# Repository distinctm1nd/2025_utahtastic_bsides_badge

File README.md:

# 2025 Utahtastic BSides Badge

Key Features:

    - ESP32-S3-WROOM Microcontroller
    - LoRa 
    - 25 Addressable LEDs
    - TFT Display
    - Power Options: Powered via Micro USB or 3 AA batteries (regulated at 3.3V).
    - Hackable and Programmable: Easily program with just a laptop and a Micro USB cable.
    - Expansion Ready: 3 minibadge slots for future add-ons.
    - Custom Meshtastic Firmware: Open-source firmware designed for mesh networking.
    - Convenient Controls – UART connection point, Reset and Flash buttons, and a power switch for toggling between USB and battery modes.
    - 4 GPIO pins available for custom dev work​

## Make sure you have the following items:

- Badge
- 6 Minibadge headers
- Battery holder
- Moon LED diffuser
- 3 AA Batteries
- Lanyard
- Minibadge kit
- Double sided foam tape

## Badge Assembly

The badge does not require further assembly to be functional by powering through the USB with an external battery. Make sure that the switch is at USB if powering with USB. 

To complete the assembly, first solder the minibadge headers to the badge. Be careful while soldering the header that is near the display. 

After this, solder the battery holder and apply foam tape to hold the end without solder connectors in place. 

Use hot glue to attach the moon diffuser to moon on the back of the badge. 

Attach the lanyard to the "post" by the raven. 

## Minibadge Assembly

- Solder the 68 ohm (1206) resistors to R1 and R2. These can be oriented any direction. 
- Solder the LEDs (yellow) to D1, D2, D3 and D4. Orientation on these matters. The green mark is on the cathode side of the LED so it needs to be oriented toward the cathode side on the PCB. The cathode side on the PCB is marked by a box around it. 

- Solder the headers to the four corners. 

## Keyboard Functionality

5-Way Switch
- Up: send message
- Down: erase/backspace
- Left: move cursor left
- Right: move cursor right
- Press: switch screens

## STL Files for joystick button cap and moon diffuser

[Joystick Button Cap](https://www.printables.com/model/1166931-joystick-cap-for-b-sides-utah-2025-badge)

[Moon Diffuser](https://www.printables.com/model/1166783-moon-led-diffuser-for-b-sides-utah-2025-badge)

## A few notes on usage

Don't transmit without the antenna attached as you could damage the badge. 

If you download the meshtastic app you can connect to your badge via bluetooth and send /receive messages through the app. You can also change many setting through the app. 

Make sure that you are on the Medium Fast channel for the conference. 

To change the moon LED color or brightness, in the app, go to:
- Radio Configuration -> Ambient Lighting

Once in the ambient lighting config you can change the brightness of the moon LEDs by changing "Current" to a different number. 255 is max brightness and anything less than that is dimmer. You can change the color codes for Red, Green and Blue to generate different colors. 

If you can't send or receive messages make sure that the LoRa channel is not on long fast. For the conference we'll be using medium fast. 

If the badge doesn't start up when turned on then push the reset button.

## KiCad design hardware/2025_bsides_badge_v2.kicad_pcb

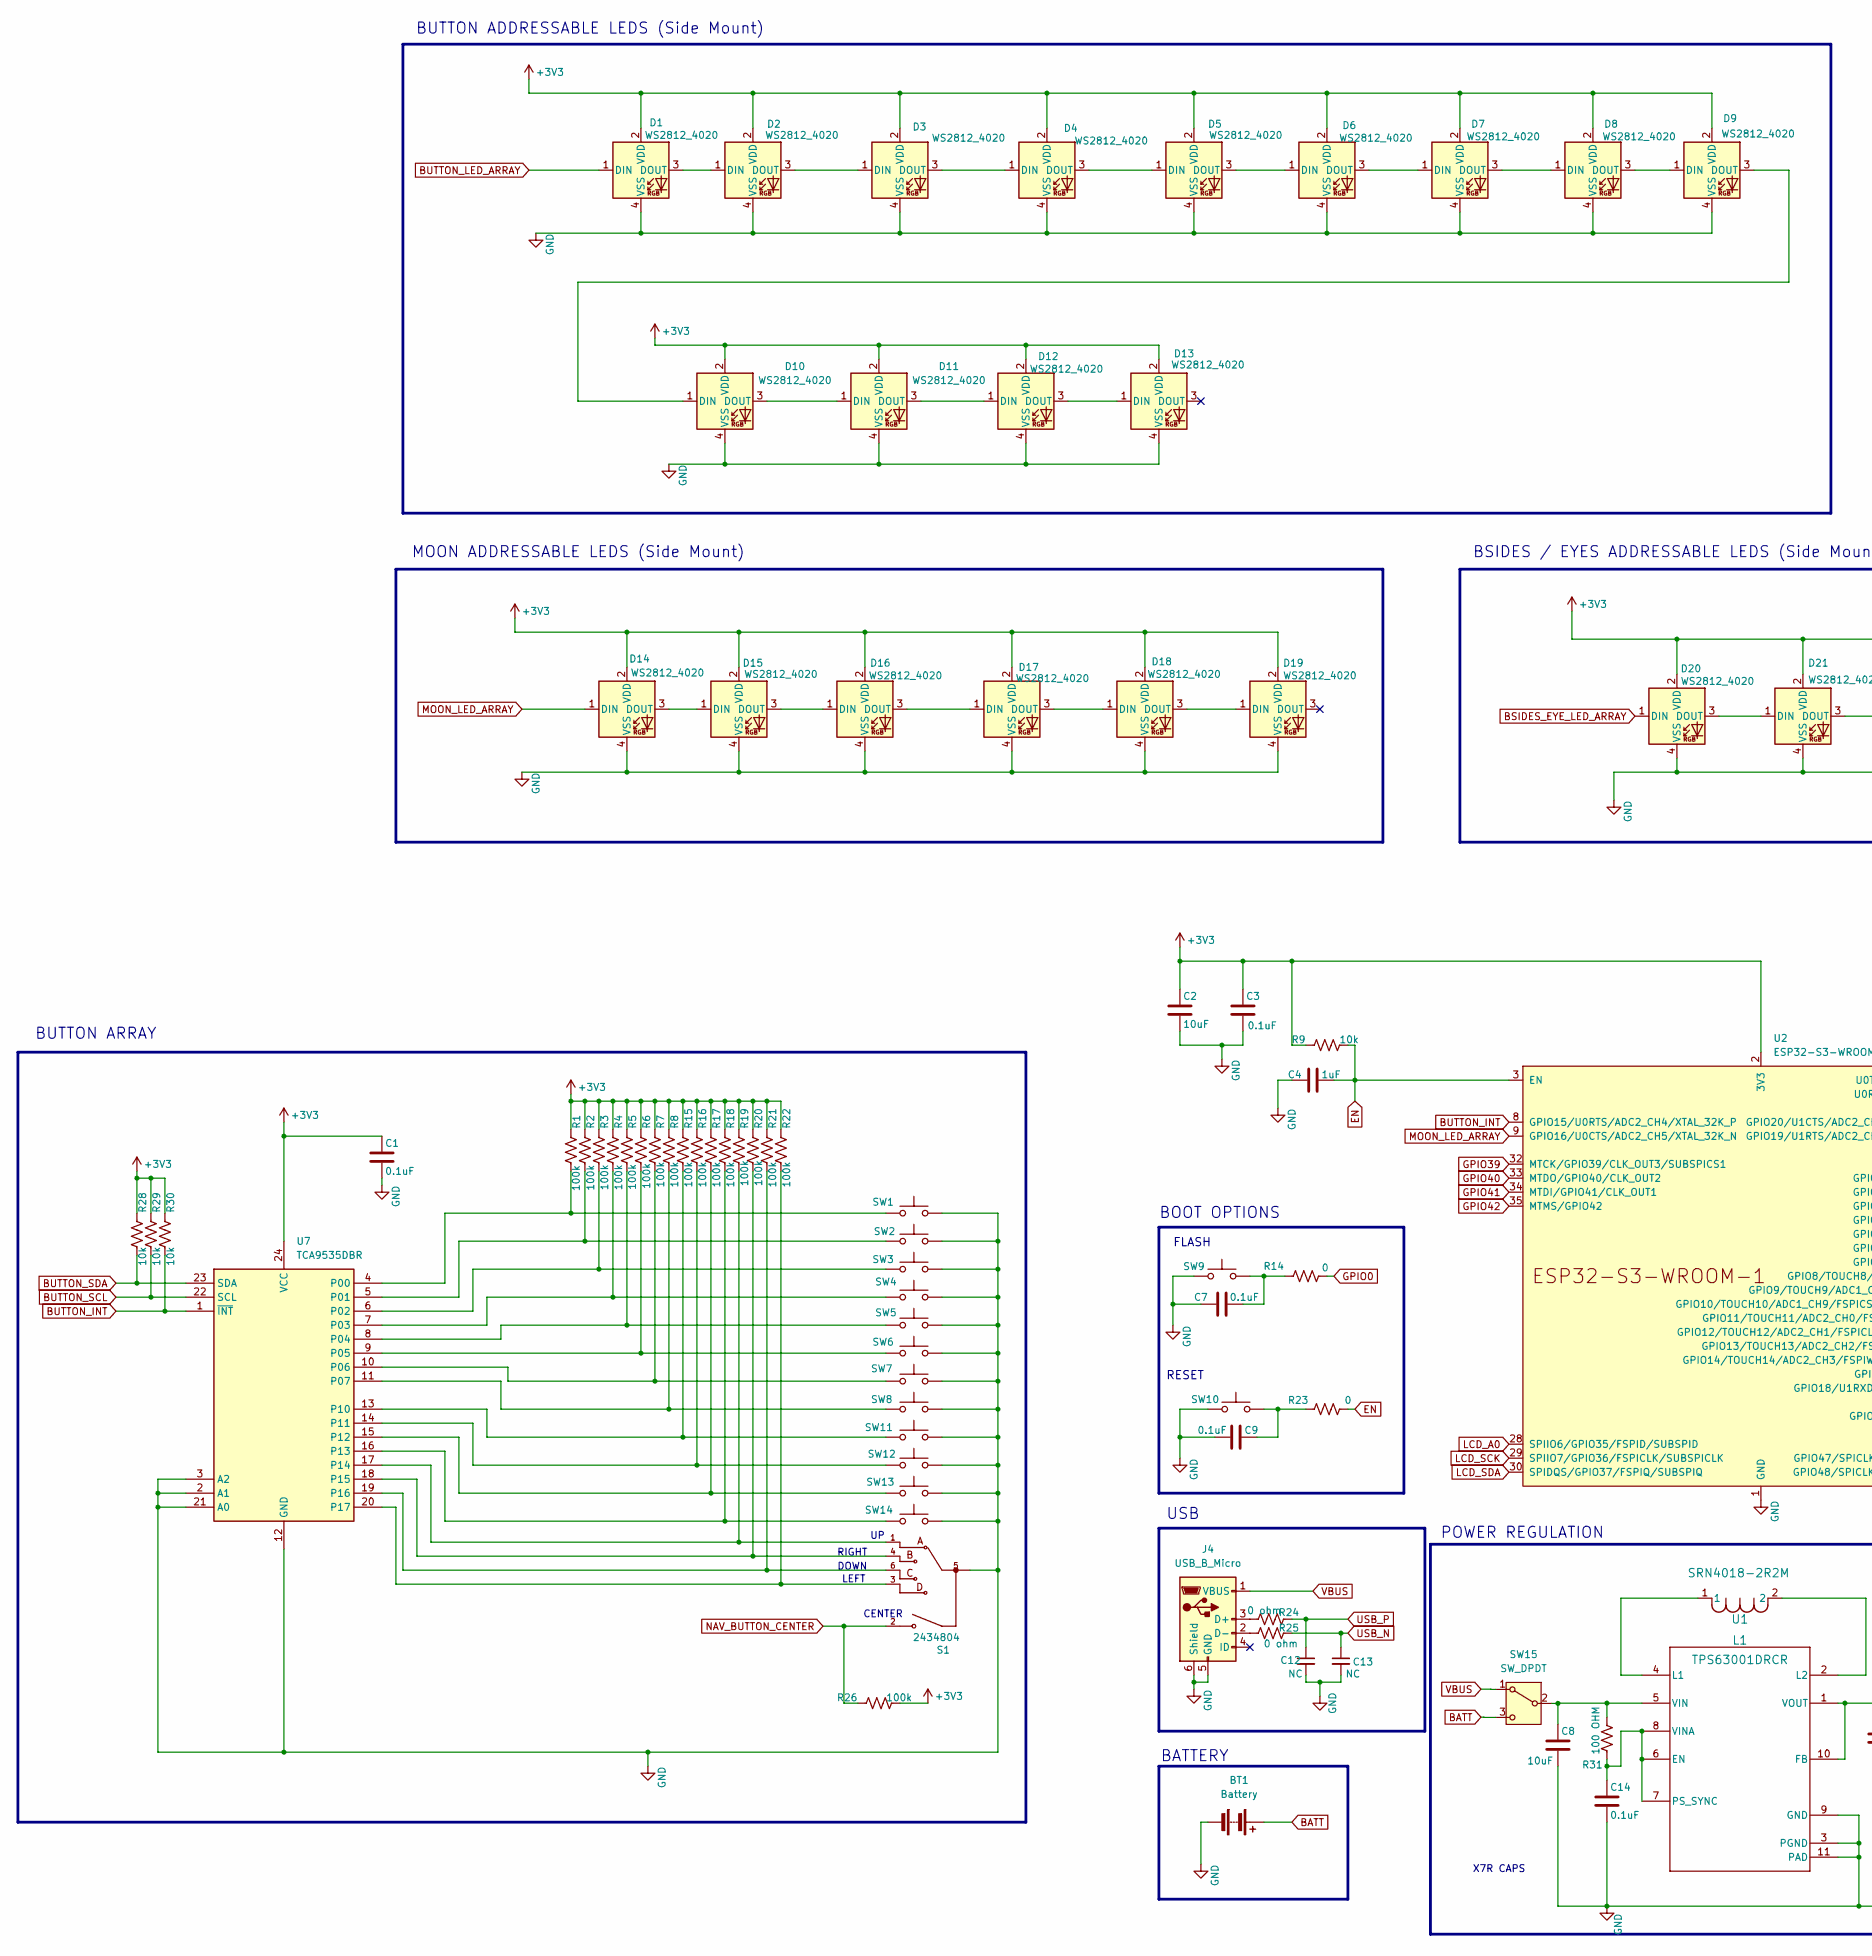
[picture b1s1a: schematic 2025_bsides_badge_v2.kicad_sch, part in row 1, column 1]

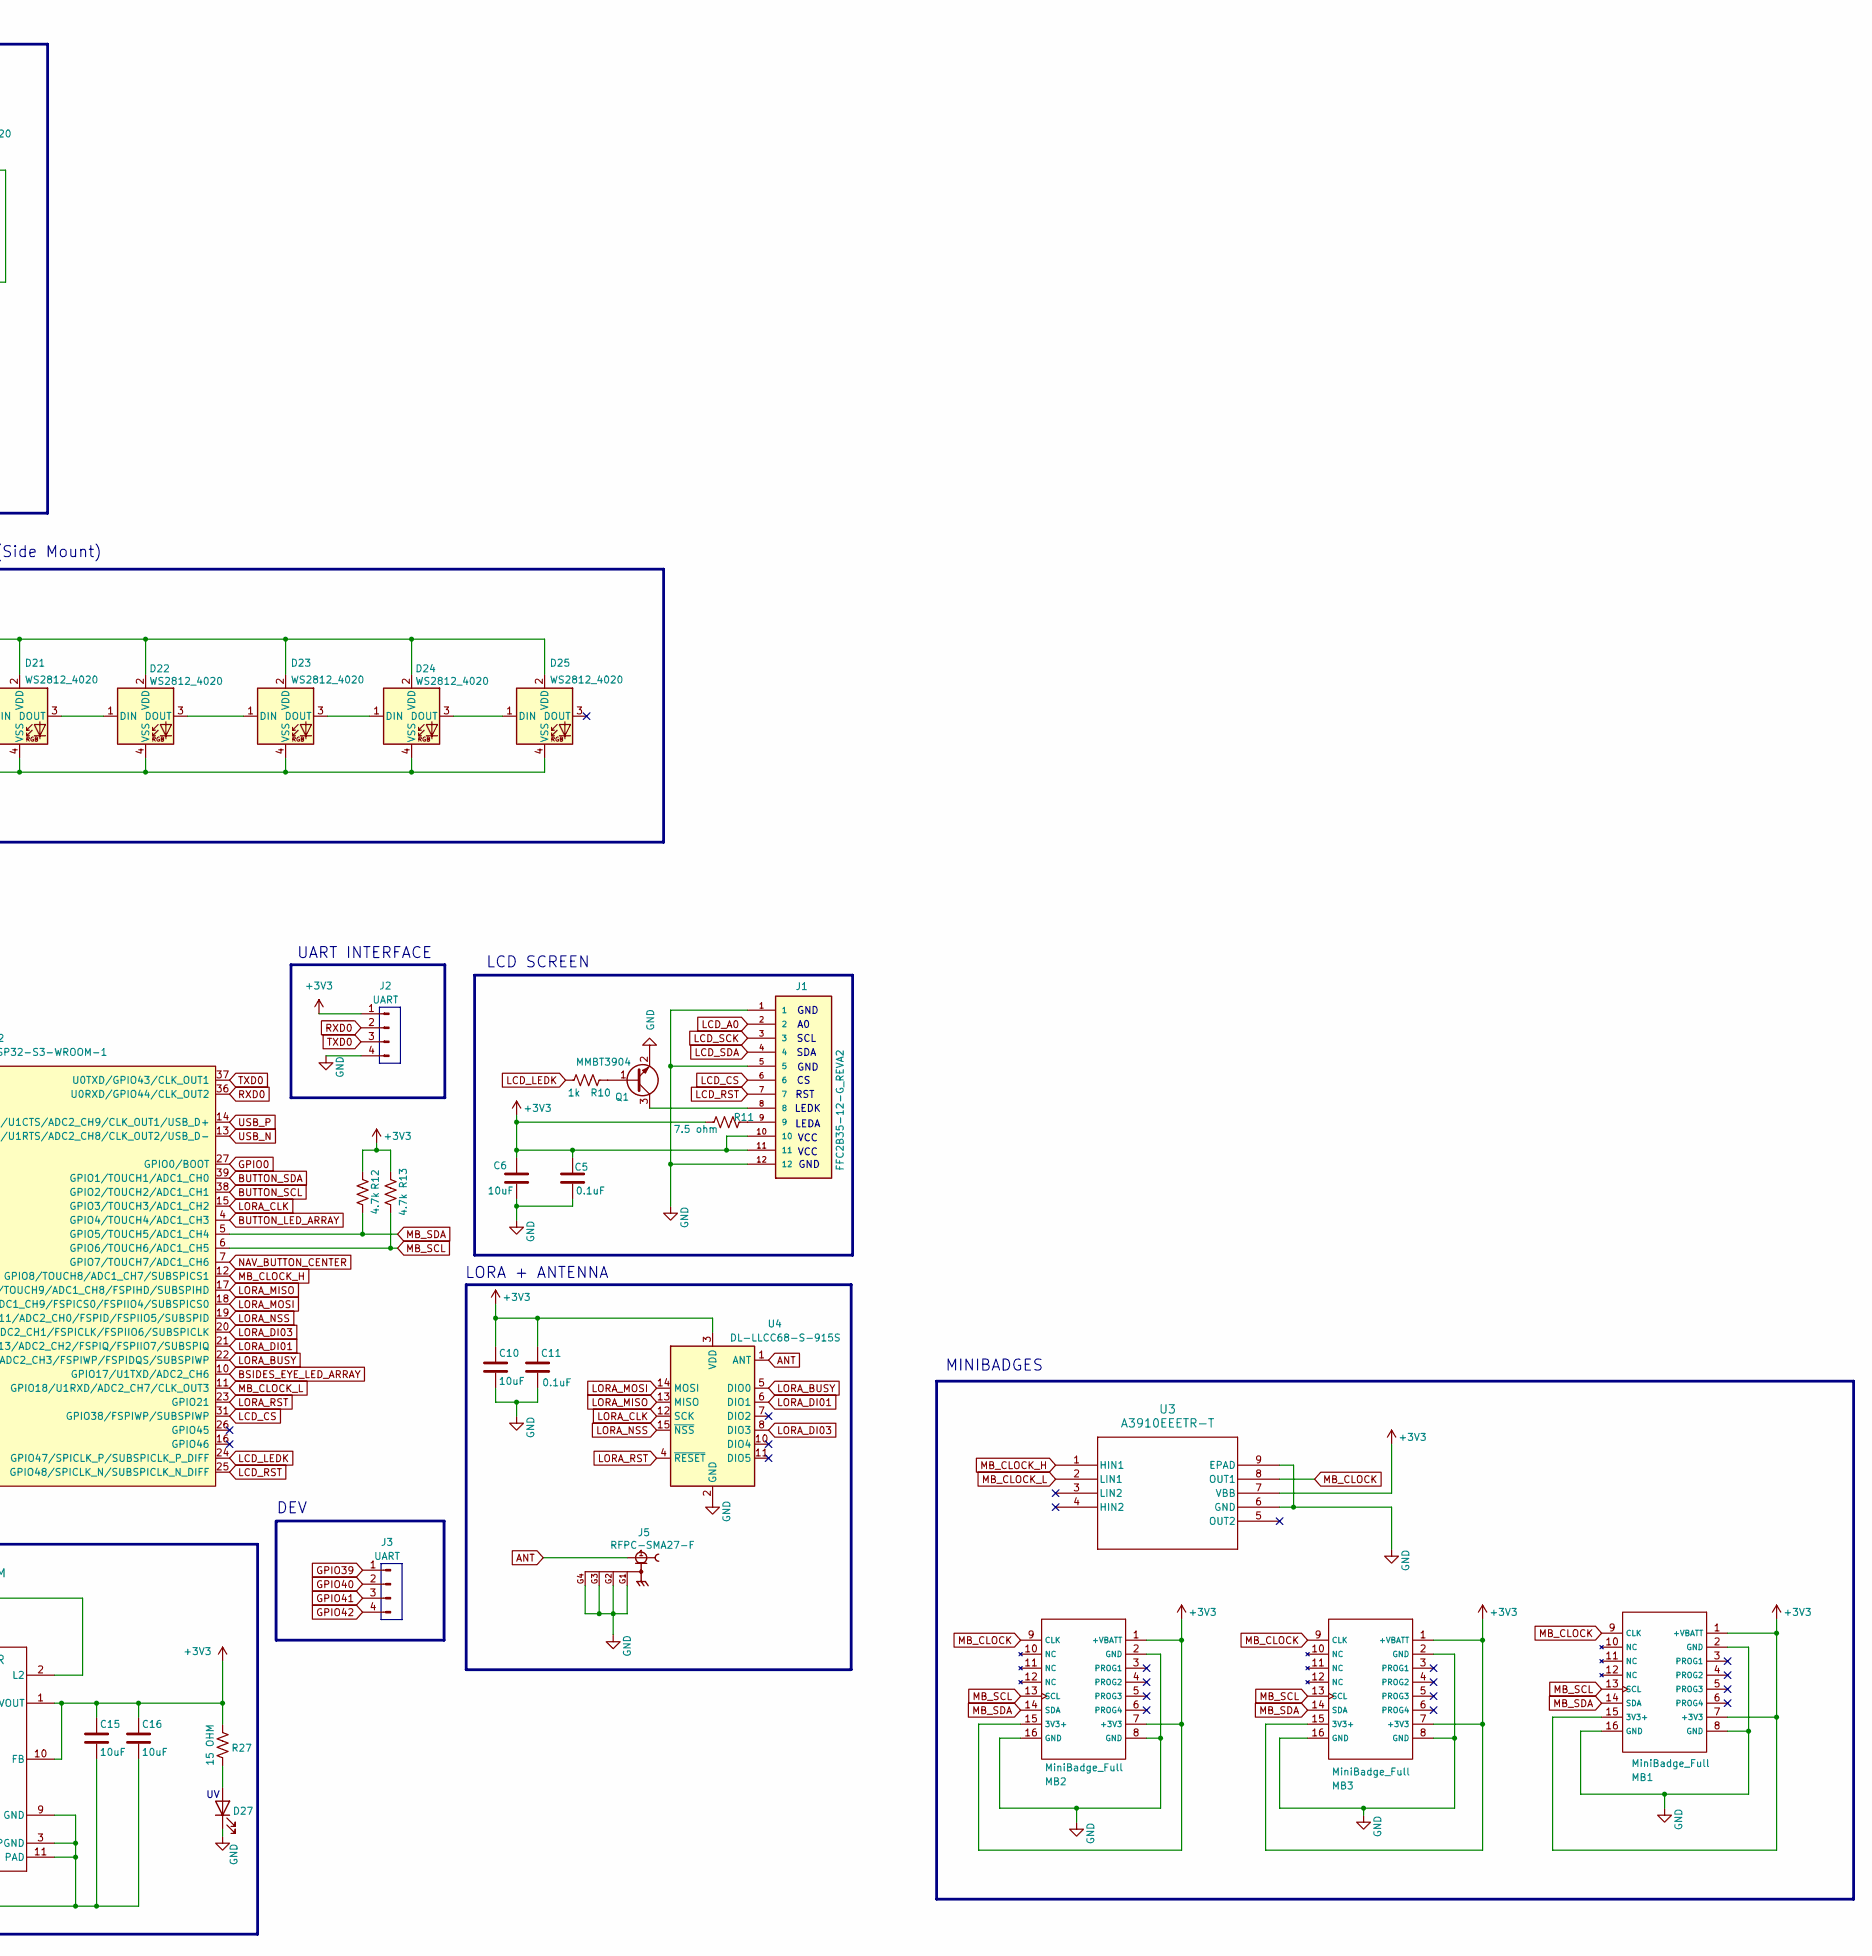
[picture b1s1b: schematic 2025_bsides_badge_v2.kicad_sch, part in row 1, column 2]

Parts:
BT1: Battery; mad_hatter_3_AA_battery
C1, C3, C5, C7, C9, C11, C14: 0.1uF; C_0603_1608Metric_Pad1.08x0.95mm_HandSolder
C2, C6, C8, C10, C15, C16: 10uF; C_0805_2012Metric_Pad1.18x1.45mm_HandSolder
C4: 1uF; C_0603_1608Metric_Pad1.08x0.95mm_HandSolder
C12, C13: NC; C_0603_1608Metric_Pad1.08x0.95mm_HandSolder
D1, D2, D3, D4, D5, D6, D7, D8, D9, D10, D11, D12, D13, D14, D15, D16, D17, D18, D19, D20, D21, D22, D23, D24, D25: WS2812_4020; sk6812-side-a
D27: LED; LED_1206_3216Metric_Pad1.42x1.75mm_HandSolder
J1: FFC2B35-12-G_REVA2; GCT_FFC2B35-12-G_REVA2; PARTREV A2
J2, J3: UART; mad_hatter_sneaky_uart_connector
J4: USB_B_Micro; USB_Micro-B_Amphenol_10118193-0001LF_Horizontal
J5: RFPC-SMA27-F; bsides_RFPC_SMA27_F; PARTREV 1.0
L1: SRN4018-2R2M; L_Bourns-SRN4018
MB1, MB2, MB3: MiniBadge_Full; MiniBadge_Slot_Basic
Q1: MMBT3904; SOT-23
R1, R2, R3, R4, R5, R6, R7, R8, R15, R16, R17, R18, R19, R20, R21, R22, R26: 100k; R_0603_1608Metric_Pad0.98x0.95mm_HandSolder
R9, R28, R29, R30: 10k; R_0603_1608Metric_Pad0.98x0.95mm_HandSolder
R10: 1k; R_0603_1608Metric_Pad0.98x0.95mm_HandSolder
R11: 7.5 ohm; R_0603_1608Metric_Pad0.98x0.95mm_HandSolder
R12, R13: 4.7k; R_0603_1608Metric_Pad0.98x0.95mm_HandSolder
R14, R23: 0; R_0603_1608Metric_Pad0.98x0.95mm_HandSolder
R24, R25: 0 ohm; R_0603_1608Metric_Pad0.98x0.95mm_HandSolder
R27: 15 OHM; R_0603_1608Metric_Pad0.98x0.95mm_HandSolder
R31: 100 OHM; R_0603_1608Metric_Pad0.98x0.95mm_HandSolder
S1: 2434804; nav_switch_2434804_1; PARTREV A
SW1, SW2, SW3, SW4, SW5, SW6, SW7, SW8, SW9, SW10, SW11, SW12, SW13, SW14: SW_Push; button_switch_TL3305A
SW15: SW_DPDT; js202011jaqn
U1: TPS63001DRCR; Texas_DRC0010J
U2: ESP32-S3-WROOM-1
U3: A3910EEETR-T; DFN-8_ALM
U4: DL-LLCC68-S-915S; Ai-Thinker-Ra-01-LoRa
U7: TCA9535DBR; SSOP-24_5.3x8.2mm_P0.65mm

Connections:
+3V3: C1.1, C2.1, C3.1, C5.1, C6.1, C10.1, C11.1, C15.1, C16.1, D1.2 (VDD), D2.2 (VDD), D3.2 (VDD), D4.2 (VDD), D5.2 (VDD), D6.2 (VDD), D7.2 (VDD), D8.2 (VDD), D9.2 (VDD), D10.2 (VDD), D11.2 (VDD), D12.2 (VDD), D13.2 (VDD), D14.2 (VDD), D15.2 (VDD), D16.2 (VDD), D17.2 (VDD), D18.2 (VDD), D19.2 (VDD), D20.2 (VDD), D21.2 (VDD), D22.2 (VDD), D23.2 (VDD), D24.2 (VDD), D25.2 (VDD), J1.10, J1.11, J2.1, MB1.1 (+VBATT), MB1.7 (+3V3), MB1.15 (3V3+), MB2.1 (+VBATT), MB2.7 (+3V3), MB2.15 (3V3+), MB3.1 (+VBATT), MB3.7 (+3V3), MB3.15 (3V3+), R1.1, R2.1, R3.1, R4.1, R5.1, R6.1, R7.1, R8.1, R9.1, R11.1, R12.2, R13.2, R15.1, R16.1, R17.1, R18.1, R19.1, R20.1, R21.1, R22.1, R26.2, R27.1, R28.1, R29.1, R30.1, U1.1 (VOUT), U1.10 (FB), U2.2 (3V3), U3.7 (VBB), U4.3 (VDD), U7.24 (VCC)
ANT: J5.1, U4.1 (ANT)
BATT: BT1.1 (+), SW15.3 (C)
BSIDES_EYE_LED_ARRAY: D20.1 (DIN), U2.10 (GPIO17/U1TXD/ADC2_CH6)
BUTTON_INT: R30.2, U2.8 (GPIO15/U0RTS/ADC2_CH4/XTAL_32K_P), U7.1 (~INT)
BUTTON_LED_ARRAY: D1.1 (DIN), U2.4 (GPIO4/TOUCH4/ADC1_CH3)
BUTTON_SCL: R29.2, U2.38 (GPIO2/TOUCH2/ADC1_CH1), U7.22 (SCL)
BUTTON_SDA: R28.2, U2.39 (GPIO1/TOUCH1/ADC1_CH0), U7.23 (SDA)
EN: C4.1, R9.2, R23.2, U2.3 (EN)
GND: BT1.2 (-), C1.2, C2.2, C3.2, C4.2, C5.2, C6.2, C7.2, C8.2, C9.2, C10.2, C11.2, C12.2, C13.2, C14.2, C15.2, C16.2, D1.4 (VSS), D2.4 (VSS), D3.4 (VSS), D4.4 (VSS), D5.4 (VSS), D6.4 (VSS), D7.4 (VSS), D8.4 (VSS), D9.4 (VSS), D10.4 (VSS), D11.4 (VSS), D12.4 (VSS), D13.4 (VSS), D14.4 (VSS), D15.4 (VSS), D16.4 (VSS), D17.4 (VSS), D18.4 (VSS), D19.4 (VSS), D20.4 (VSS), D21.4 (VSS), D22.4 (VSS), D23.4 (VSS), D24.4 (VSS), D25.4 (VSS), D27.1 (K), J1.1, J1.5, J1.12, J2.4, J4.5 (GND), J4.6 (Shield), J5.G1, J5.G2, J5.G3, J5.G4, MB1.2 (GND), MB1.8 (GND), MB1.16 (GND), MB2.2 (GND), MB2.8 (GND), MB2.16 (GND), MB3.2 (GND), MB3.8 (GND), MB3.16 (GND), Q1.2 (E), S1.5, SW1.2, SW2.2, SW3.2, SW4.2, SW5.2, SW6.2, SW7.2, SW8.2, SW9.1, SW10.1, SW11.2, SW12.2, SW13.2, SW14.2, U1.3 (PGND), U1.9 (GND), U1.11 (PAD), U2.1 (GND), U2.40 (GND), U2.41 (GND), U3.6 (GND), U3.9 (EPAD), U4.2 (GND), U4.9 (GND), U4.16 (GND), U7.2 (A1), U7.3 (A2), U7.12 (GND), U7.21 (A0)
GPIO0: R14.2, U2.27 (GPIO0/BOOT)
GPIO39: J3.1, U2.32 (MTCK/GPIO39/CLK_OUT3/SUBSPICS1)
GPIO40: J3.2, U2.33 (MTDO/GPIO40/CLK_OUT2)
GPIO41: J3.3, U2.34 (MTDI/GPIO41/CLK_OUT1)
GPIO42: J3.4, U2.35 (MTMS/GPIO42)
LCD_A0: J1.2, U2.28 (SPIIO6/GPIO35/FSPID/SUBSPID)
LCD_CS: J1.6, U2.31 (GPIO38/FSPIWP/SUBSPIWP)
LCD_LEDK: R10.1, U2.24 (GPIO47/SPICLK_P/SUBSPICLK_P_DIFF)
LCD_RST: J1.7, U2.25 (GPIO48/SPICLK_N/SUBSPICLK_N_DIFF)
LCD_SCK: J1.3, U2.29 (SPIIO7/GPIO36/FSPICLK/SUBSPICLK)
LCD_SDA: J1.4, U2.30 (SPIDQS/GPIO37/FSPIQ/SUBSPIQ)
LORA_BUSY: U2.22 (GPIO14/TOUCH14/ADC2_CH3/FSPIWP/FSPIDQS/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), U4.5 (DIO0)
LORA_CLK: U2.15 (GPIO3/TOUCH3/ADC1_CH2), U4.12 (SCK)
LORA_DI01: U2.21 (GPIO13/TOUCH13/ADC2_CH2/FSPIQ/FSPIIO7/S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), U4.6 (DIO1)
LORA_DI03: U2.20 (GPIO12/TOUCH12/ADC2_CH1/FSPICLK/FSPIIO6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), U4.8 (DIO3)
LORA_MISO: U2.17 (GPIO9/TOUCH9/ADC1_CH8/FSPIHD/SUBSPIHD), U4.13 (MISO)
LORA_MOSI: U2.18 (GPIO10/TOUCH10/ADC1_CH9/FSPICS0/FSPIIO4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), U4.14 (MOSI)
LORA_NSS: U2.19 (GPIO11/TOUCH11/ADC2_CH0/FSPID/FSPIIO5/S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), U4.15 (~NSS)
LORA_RST: U2.23 (GPIO21), U4.4 (~RESET)
MB_CLOCK: MB1.9 (CLK), MB2.9 (CLK), MB3.9 (CLK), U3.8 (OUT1)
MB_CLOCK_H: U2.12 (GPIO8/TOUCH8/ADC1_CH7/SUBSPICS1), U3.1 (HIN1)
MB_CLOCK_L: U2.11 (GPIO18/U1RXD/ADC2_CH7/CLK_OUT3), U3.2 (LIN1)
MB_SCL: MB1.13 (SCL), MB2.13 (SCL), MB3.13 (SCL), R13.1, U2.6 (GPIO6/TOUCH6/ADC1_CH5)
MB_SDA: MB1.14 (SDA), MB2.14 (SDA), MB3.14 (SDA), R12.1, U2.5 (GPIO5/TOUCH5/ADC1_CH4)
MOON_LED_ARRAY: D14.1 (DIN), U2.9 (GPIO16/U0CTS/ADC2_CH5/XTAL_32K_N)
NAV_BUTTON_CENTER: R26.1, S1.2, U2.7 (GPIO7/TOUCH7/ADC1_CH6)
unnamed: C7.1, R14.1, SW9.2
unnamed: C9.1, R23.1, SW10.2
unnamed: D1.3 (DOUT), D2.1 (DIN)
unnamed: D2.3 (DOUT), D3.1 (DIN)
unnamed: D3.3 (DOUT), D4.1 (DIN)
unnamed: D4.3 (DOUT), D5.1 (DIN)
unnamed: D5.3 (DOUT), D6.1 (DIN)
unnamed: D6.3 (DOUT), D7.1 (DIN)
unnamed: D7.3 (DOUT), D8.1 (DIN)
unnamed: D8.3 (DOUT), D9.1 (DIN)
unnamed: D9.3 (DOUT), D10.1 (DIN)
unnamed: D10.3 (DOUT), D11.1 (DIN)
unnamed: D11.3 (DOUT), D12.1 (DIN)
unnamed: D12.3 (DOUT), D13.1 (DIN)
unnamed: D14.3 (DOUT), D15.1 (DIN)
unnamed: D15.3 (DOUT), D16.1 (DIN)
unnamed: D16.3 (DOUT), D17.1 (DIN)
unnamed: D17.3 (DOUT), D18.1 (DIN)
unnamed: D18.3 (DOUT), D19.1 (DIN)
unnamed: D20.3 (DOUT), D21.1 (DIN)
unnamed: D21.3 (DOUT), D22.1 (DIN)
unnamed: D22.3 (DOUT), D23.1 (DIN)
unnamed: D23.3 (DOUT), D24.1 (DIN)
unnamed: D24.3 (DOUT), D25.1 (DIN)
unnamed: D27.2 (A), R27.2
unnamed: J1.9, R11.2
unnamed: J4.3 (D+), R24.2
unnamed: J4.2 (D-), R25.2
unnamed: Q1.1 (B), R10.2
unnamed: J1.8, Q1.3 (C)
unnamed: C8.1, R31.1, SW15.2 (B), U1.5 (VIN)
unnamed: C14.1, R31.2, U1.6 (EN), U1.7 (PS_SYNC), U1.8 (VINA)
unnamed: L1.1, U1.4 (L1)
unnamed: L1.2, U1.2 (L2)
unnamed: R1.2, SW1.1, U7.4 (P00)
unnamed: R2.2, SW2.1, U7.5 (P01)
unnamed: R3.2, SW3.1, U7.6 (P02)
unnamed: R4.2, SW4.1, U7.7 (P03)
unnamed: R5.2, SW5.1, U7.8 (P04)
unnamed: R6.2, SW6.1, U7.9 (P05)
unnamed: R7.2, SW7.1, U7.10 (P06)
unnamed: R8.2, SW8.1, U7.11 (P07)
unnamed: R15.2, SW11.1, U7.13 (P10)
unnamed: R16.2, SW12.1, U7.14 (P11)
unnamed: R17.2, SW13.1, U7.15 (P12)
unnamed: R18.2, SW14.1, U7.16 (P13)
unnamed: R19.2, S1.1, U7.17 (P14)
unnamed: R20.2, S1.4, U7.18 (P15)
unnamed: R21.2, S1.6, U7.19 (P16)
unnamed: R22.2, S1.3, U7.20 (P17)
RXD0: J2.2, U2.36 (U0RXD/GPIO44/CLK_OUT2)
TXD0: J2.3, U2.37 (U0TXD/GPIO43/CLK_OUT1)
USB_N: C13.1, R25.1, U2.13 (GPIO19/U1RTS/ADC2_CH8/CLK_OUT2/USB_D-)
USB_P: C12.1, R24.1, U2.14 (GPIO20/U1CTS/ADC2_CH9/CLK_OUT1/USB_D+)
VBUS: J4.1 (VBUS), SW15.1 (A)

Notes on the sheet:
UART INTERFACE
LORA + ANTENNA
BATTERY
LEFT
MINIBADGES
GND
DEV
USB
BUTTON ARRAY
VCC
FLASH
LCD SCREEN
MOON ADDRESSABLE LEDS (Side Mount)
POWER REGULATION
BSIDES / EYES ADDRESSABLE LEDS (Side Mount)
RESET
X7R CAPS
CENTER
BUTTON ADDRESSABLE LEDS (Side Mount)
DOWN
SDA
LEDA
BOOT OPTIONS
RIGHT
RST
SCL
LEDK

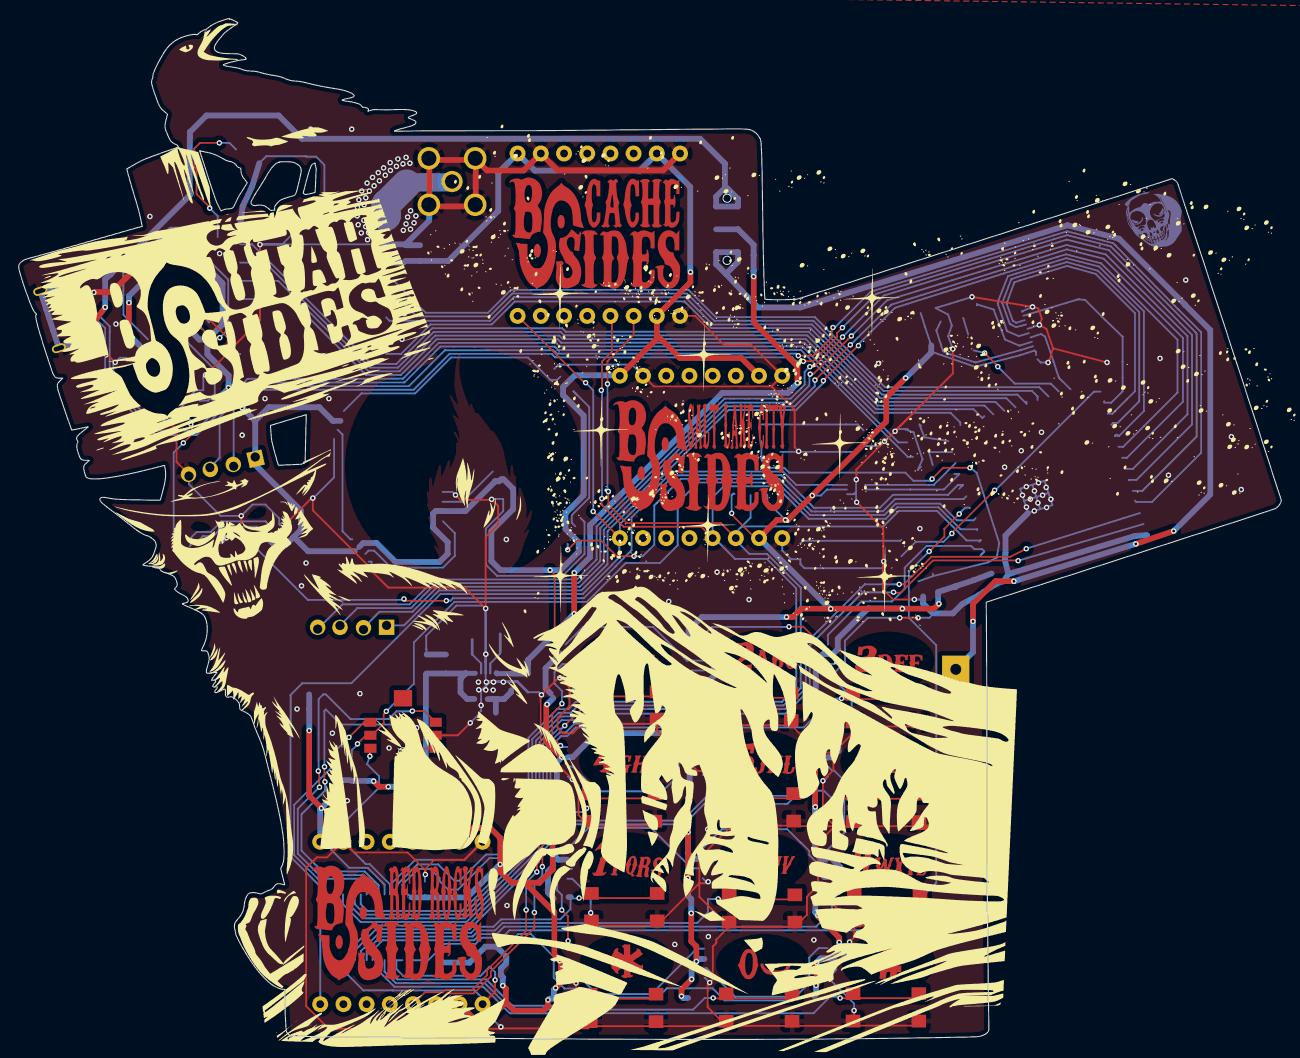
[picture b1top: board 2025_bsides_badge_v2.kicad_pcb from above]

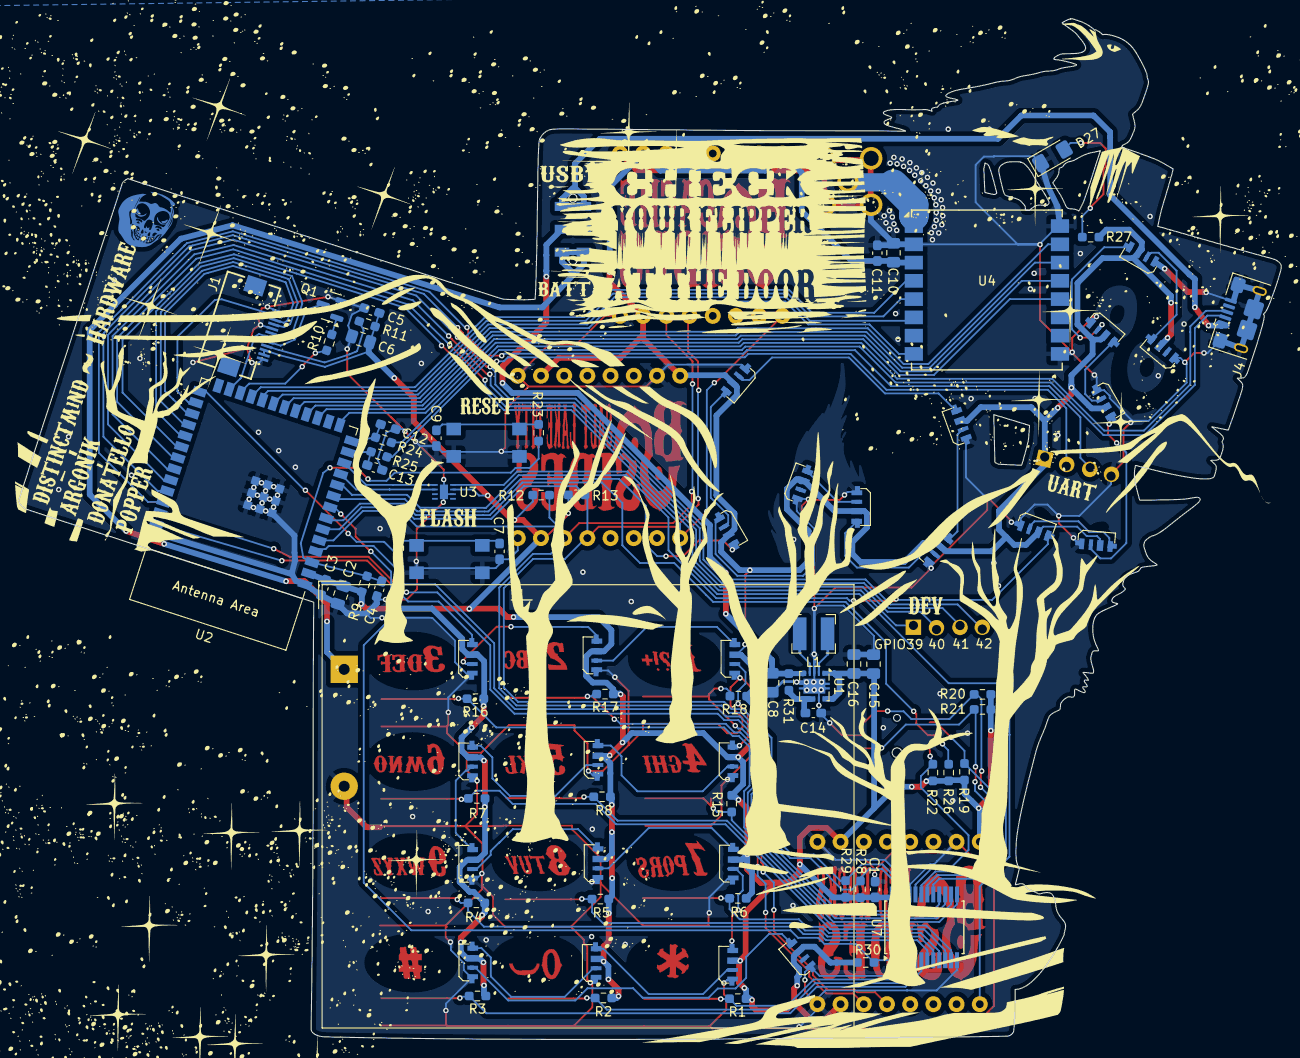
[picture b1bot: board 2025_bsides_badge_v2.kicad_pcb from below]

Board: 2 copper layers, 138.2 x 111.8 mm, 105 parts (85 on the bottom side), 91 nets.

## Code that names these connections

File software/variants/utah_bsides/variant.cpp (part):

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
// I2C Expander (TCA9535)
#define TCA9535_ADDRESS 0x20
#define BUTTON_SDA 1
#define BUTTON_SCL 2
#define BUTTON_INT 15

extern graphics::Screen *screen;

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    TickType_t xLastWakeTime;
    xLastWakeTime = xTaskGetTickCount();

    pinMode(MB_CLOCK_H, OUTPUT);
    pinMode(MB_CLOCK_L, OUTPUT);

    while (1){ 
        //Update Minibadge CLK pin
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
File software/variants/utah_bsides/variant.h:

//////////////////////////////////////////////////////////////////////////////////
//                                                                              //
//   Utah BSides Badge    //
//                                                                              //
//////////////////////////////////////////////////////////////////////////////////
#include <Adafruit_NeoPixel.h>


#define HAS_WIFI 1
#define HAS_BLUETOOTH 1

#define HAS_RADIO 1

#define HAS_GPS 0

#define CANNED_MESSAGE_MODULE_ENABLE 1

//LORA MODULE
#define USE_LLCC68
#define USE_SX1262

//LORA SPI
#define LORA_SCK 3              
#define LORA_MOSI 10                 
#define LORA_MISO 9 
#define LORA_CS 11

//LORA CONFIG
#define SX126X_CS LORA_CS         // module's NSS pin                
#define SX126X_BUSY 14                
#define SX126X_DIO1 13  
#define SX126X_RESET 21      

#define LORA_FREQUENCY 915000000


// Display

#define HAS_SCREEN 1 

// ST7735S TFT LCD
#define ST7735S 1 // there are different (sub-)versions of ST7735
#define ST7735_CS 38
#define ST7735_RS 35  // DC
#define ST7735_SDA 37 // MOSI
#define ST7735_SCK 36
#define ST7735_RESET 48
#define ST7735_MISO -1
#define ST7735_BUSY -1
#define TFT_BL 47
#define ST7735_SPI_HOST SPI3_HOST 
#define SPI_FREQUENCY 40000000
#define SPI_READ_FREQUENCY 16000000
#define TFT_HEIGHT 160
#define TFT_WIDTH 128
#define TFT_OFFSET_X 2
#define TFT_OFFSET_Y -1
#define TFT_INVERT false
#define SCREEN_ROTATE
#define SCREEN_TRANSITION_FRAMERATE 5 // fps
#define DISPLAY_FORCE_SMALL_FONTS
#define TFT_BACKLIGHT_ON HIGH


//LEDs
//Moon LEDs: These can be adjusted with the app
#define HAS_NEOPIXEL                         // Enable the use of neopixels
#define NEOPIXEL_COUNT 6                     // How many neopixels are connected
#define NEOPIXEL_DATA 16                      // gpio pin used to send data to the neopixels
#define NEOPIXEL_TYPE (NEO_GRB + NEO_KHZ800) // type of neopixels in use
#define ENABLE_AMBIENTLIGHTING               // Turn on Ambient Lighting

//Logo, Eye, Button LEDs
#define BUTTON_LED_PIN 4
#define BUTTON_LED_COUNT 13
#define LOGO_EYE_LED_PIN 17
#define LOGO_EYE_LED_COUNT 6

//LED Functions
//void initVariantHardware();
void handleButtonLedFlashing();
void handleChasingLedPatterns();

extern Adafruit_NeoPixel button_leds;
extern Adafruit_NeoPixel logo_eye_leds;

// All buttons including 5 way nav use the TCA9535 GPIO Expander 
//EXCEPT center NAV button is on following pin GPIO 7
//
//I2C
#define I2C_SDA 1
#define I2C_SCL 2



#define ENABLE_AMBIENTLIGHTING               // Turn on Ambient Lighting
// #define BUTTON1_COLOR 0xFF0000               // Background light for Button 1 in HEX RGB Color (RadioMaster Bandit only).
// #define BUTTON1_COLOR_INDEX 0                // NeoPixel Index ID for Button 1
// #define BUTTON2_COLOR 0x0000FF               // Background light for Button 2 in HEX RGB Color (RadioMaster Bandit only).
// #define BUTTON2_COLOR_INDEX 1                // NeoPixel Index ID for Button 2

/*
  It has 1 x five-way and 2 x normal buttons.

  Button    GPIO    RGB Index
  ---------------------------
  Five-way  39      -
  Button 1  34      0
  Button 2  35      1

  Five way button when using ADC.
  2.632V, 2.177V, 1.598V, 1.055V, 0V

  ADC Values:
  { UP, DOWN, LEFT, RIGHT, ENTER, IDLE }
  3227, 0 ,1961, 2668, 1290, 4095

  Five way button when using ADC.
  https://github.com/ExpressLRS/targets/blob/f3215b5ec891108db1a13523e4163950cfcadaac/TX/Radiomaster%20Bandit.json#L41

*/
//#define INPUTBROKER_EXPRESSLRSFIVEWAY_TYPE
//#define PIN_JOYSTICK 7
//#define JOYSTICK_ADC_VALS /*UP*/ 3227, /*DOWN*/ 0, /*LEFT*/ 1961, /*RIGHT*/ 2668, /*OK*/ 1290, /*IDLE*/ 4095


// keyboard
/*#define INPUTBROKER_SERIAL_TYPE 1
#define KB_LOAD 21 // load values from the switch and store in shift register
#define KB_CLK 22  // clock pin for serial data out
#define KB_DATA 23 // data pin
#define CANNED_MESSAGE_MODULE_ENABLE 1
*/

/*
 Normal Button Pin setup.
*/
#define BUTTON_PIN 7
//#define BUTTON_NEED_PULLUP

//Buzzer
//#define PIN_BUZZER  //Add pin number for buzzer. 39, 40, 41, 42


#define UART_TX 43
#define UART_RX 44


//Minibadge Clock Signal
#define MB_CLOCK_H 8
#define MB_CLOCK_L 18

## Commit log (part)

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2024-09-13 first commit with project structure
2024-11-23 Create delete
2024-11-23 Create test
2024-12-02 Readd files from upstream
2024-12-02 Add UpDown file
2024-12-06 Update variant.h
    changing back to original code
2024-12-06 Update platformio.ini
    changing back to original code
2024-12-06 Update variant.h
    updated spi host to sp3_host for display
2024-12-06 Update architecture.h
    updated LoRa SPI settings and SERIAL0_RX_GPIO
2024-12-06 Update variant.h
    update UART pins
2024-12-07 Update mesh.proto
    comment out custom proto
2024-12-07 Update platformio.ini
    change back to PRIVATE_HW
2024-12-07 Update architecture.h
    comment out UTAH_BSIDES board
2025-01-10 fixes
2025-01-19 partial button implementation.
2025-01-25 more button code.
2025-01-31 Add files via upload
    final schematic and pcb files
2025-01-31 Add files via upload
    gerber files
2025-02-01 Update userPrefs.h
    update user preferences for splash screen and channels
2025-02-01 Update variant.cpp
    add LED functionality
2025-02-01 Update variant.h
    add LED functionality
2025-02-01 Update AmbientLightingThread.h
    private_hw for LEDs
2025-02-02 Update variant.cpp
    add ledsoff option to turn off leds
2025-02-02 Update variant.h
    add neopixel library
2025-02-06 Added minibadge clock
2025-02-06 multi-press support
2025-02-06 Group keyboard code together.
2025-02-08 key changes: up for sending, down for erasing. Add bottom left and right buttons.
2025-02-12 specify pin mode for clock pins
2025-02-14 Enabled channel 1 (BSIDESMyself)
2025-03-14 reset lora on init
2025-03-20 Fix display offset
2025-04-07 Fix keyboard hang by using polling instead of interrupts.
2025-04-09 Fix multi-press and konami code
2025-04-09 Update README.md
    update readme
2025-04-09 Adds SX1262 for second batch of lora modules
2025-04-09 Open the preferences menu by long pressing * to change LED cycles. Also fixes konami code display.
2025-04-09 welcome screen tips
2025-04-09 fix critical error caused by userprefs. Fix menu bug. Add menu option to factory reset.
2025-04-09 Set default channel to medium fast
